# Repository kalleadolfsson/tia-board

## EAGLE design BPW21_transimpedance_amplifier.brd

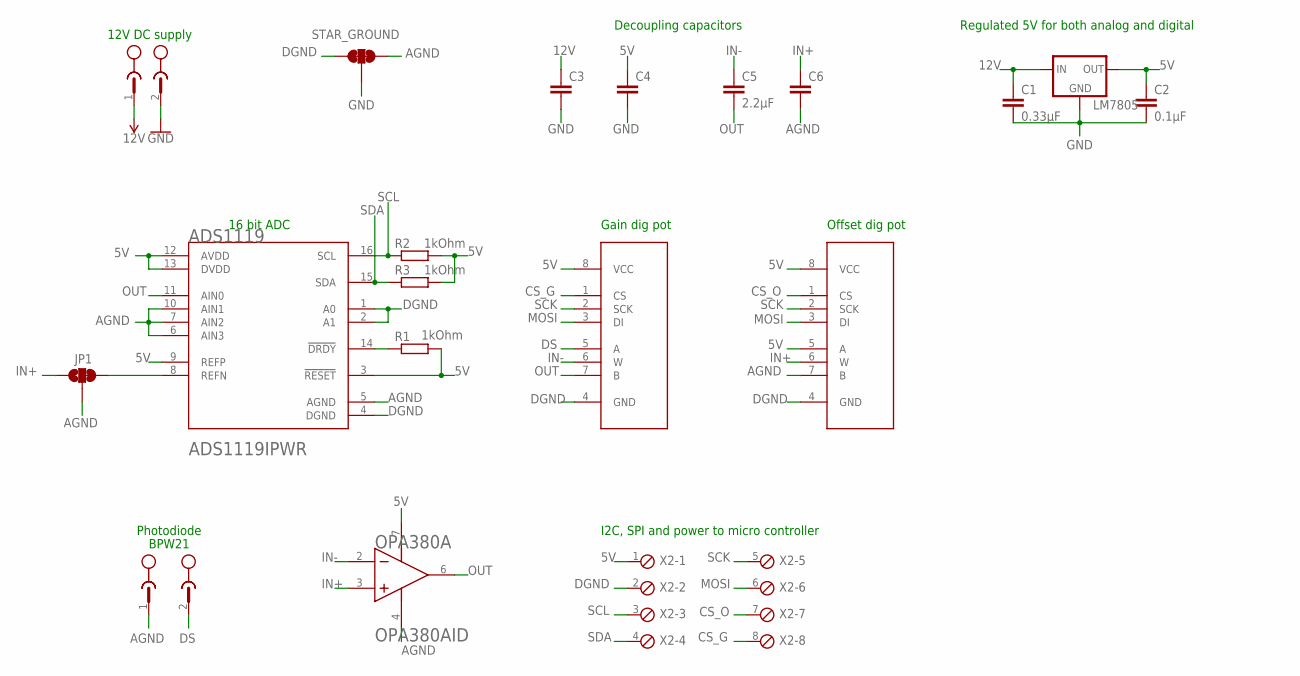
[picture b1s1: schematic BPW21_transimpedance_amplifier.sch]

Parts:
ADS1119: TEXAS_INSTRUMENTS_ADS1119IPWRTEXAS_INSTRUMENTS_AD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; TEXAS_INSTRUMENTS_ADS1119IPWR_3
BPW21: MSTBA2
C1: 0.33µF; C0805
C2: 0.1µF; C0805
C3, C4, C6: C-EUC0805; C0805
C5: 2.2µF; C0805
GAIN_POT: MCP41XXX; DIP08
JP1: JUMPER-SMT_3_1-NC_TRACE_NO-SILK; SMT-JUMPER_3_1-NC_TRACE_NO-SILK
LM7805: V_REG_78XX7812; TO-252
OFFSET_POT: MCP41XXX; DIP08
OPA380: TEXAS_INSTRUMENTS_OPA380AIDTEXAS_INSTRUMENTS_OPA3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; TEXAS_INSTRUMENTS_OPA380AID_1
R1, R2, R3: 1kOhm; R0805
STAR_GROUND: JUMPER-SMT_3_2-NC_TRACE_NO-SILK; SMT-JUMPER_3_2-NC_TRACE_NO-SILK
X2: MPT8; 8POL254
X4: MSTBA2

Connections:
5V: ADS1119.3 (!RESET!), ADS1119.9 (REFP), ADS1119.12 (AVDD), ADS1119.13 (DVDD), C2.1, C4.1, GAIN_POT.8 (VCC), LM7805.2 (OUT), OFFSET_POT.5 (A), OFFSET_POT.8 (VCC), OPA380.7 (V+), R1.2, R2.2, R3.2, X2.1
12V: C1.1, C3.1, LM7805.1 (IN), X4.1
AGND: ADS1119.5 (AGND), ADS1119.6 (AIN3), ADS1119.7 (AIN2), ADS1119.10 (AIN1), BPW21.1, C6.2, JP1.2, OFFSET_POT.7 (B), OPA380.4 (V-), STAR_GROUND.3
CS_G: GAIN_POT.1 (CS), X2.8
CS_O: OFFSET_POT.1 (CS), X2.7
DGND: ADS1119.1 (A0), ADS1119.2 (A1), ADS1119.4 (DGND), GAIN_POT.4 (GND), OFFSET_POT.4 (GND), STAR_GROUND.1, X2.2
DS: BPW21.2, GAIN_POT.5 (A)
GND: C1.2, C2.2, C3.2, C4.2, LM7805.3 (GND), STAR_GROUND.2, X4.2
IN+: C6.1, JP1.1, OFFSET_POT.6 (W), OPA380.3 (IN+)
IN-: C5.1, GAIN_POT.6 (W), OPA380.2 (IN-)
MOSI: GAIN_POT.3 (DI), OFFSET_POT.3 (DI), X2.6
unnamed: ADS1119.14 (!DRDY!), R1.1
OUT: ADS1119.11 (AIN0), C5.2, GAIN_POT.7 (B), OPA380.6 (OUT)
REFN: ADS1119.8 (REFN), JP1.3
SCK: GAIN_POT.2 (SCK), OFFSET_POT.2 (SCK), X2.5
SCL: ADS1119.16 (SCL), R2.1, X2.3
SDA: ADS1119.15 (SDA), R3.1, X2.4

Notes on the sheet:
Photodiode
BPW21
12V DC supply
Gain dig pot
Offset dig pot
16 bit ADC
Regulated 5V for both analog and digital
Decoupling capacitors
I2C, SPI and power to micro controller

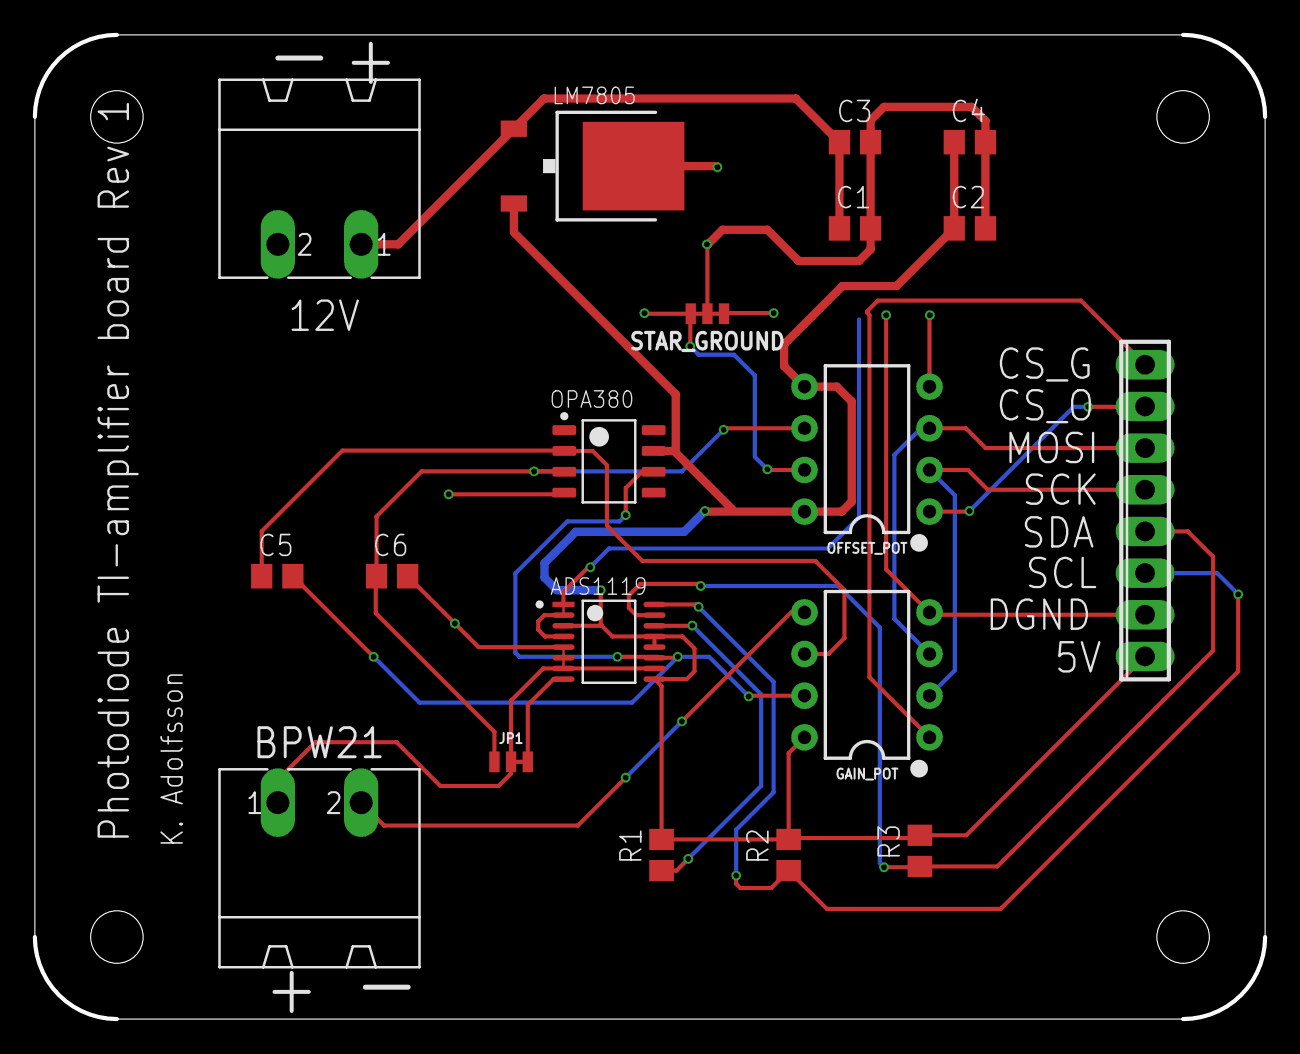
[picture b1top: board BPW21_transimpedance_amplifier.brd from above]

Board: 2 copper layers, 75.0 x 60.0 mm, 19 parts (0 on the bottom side), 17 nets.

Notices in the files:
parts and their libraries:
SparkFun-IC-Special-Function: Licensing: Creative Commons ShareAlike 4.0 International - https://creativecommons.org/licenses/by-sa/4.0
